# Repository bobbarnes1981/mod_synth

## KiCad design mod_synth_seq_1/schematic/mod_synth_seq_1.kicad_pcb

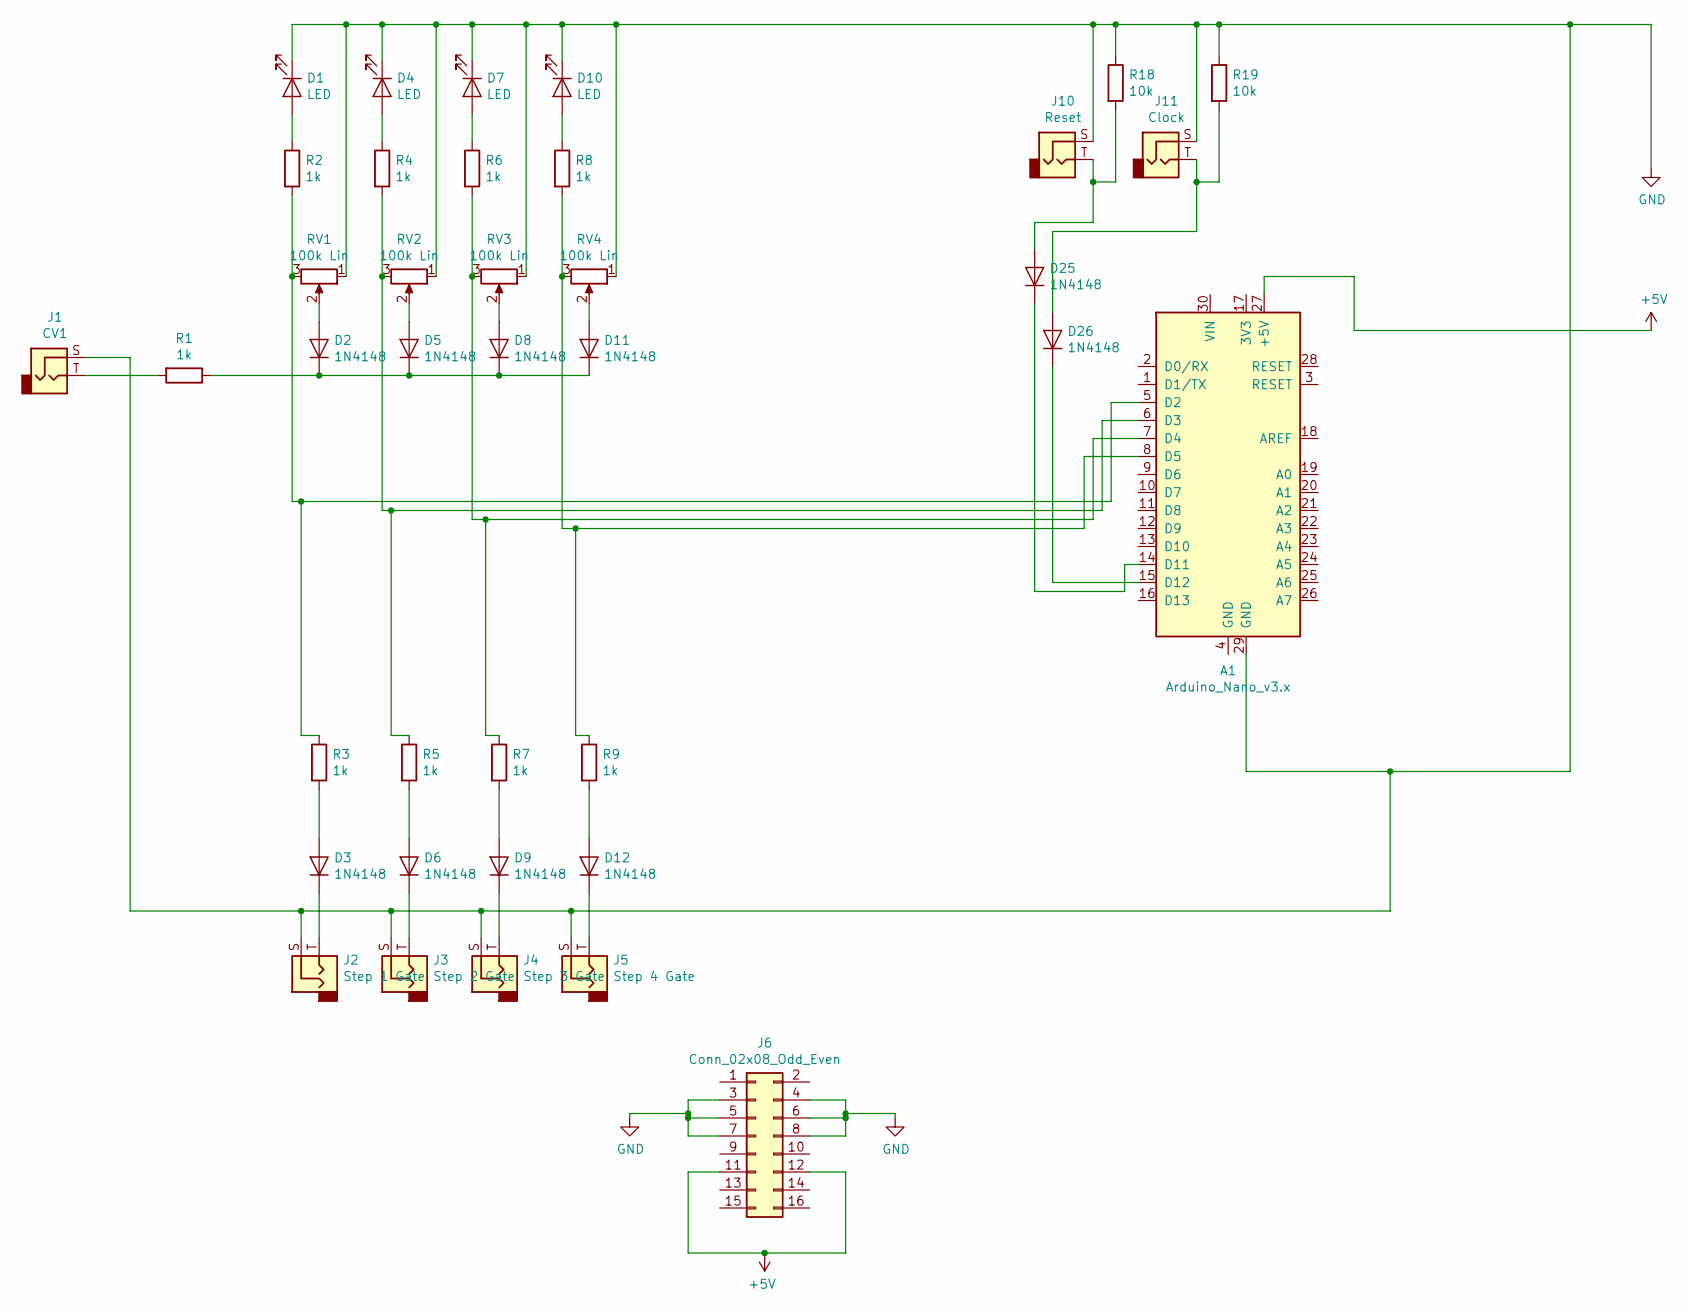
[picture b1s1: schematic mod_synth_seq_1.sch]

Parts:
A1: Arduino_Nano_v3.x; Arduino_Nano
D1, D4, D7, D10: LED; LED_D5.0mm
D2, D3, D5, D6, D8, D9, D11, D12, D25, D26: 1N4148; D_DO-35_SOD27_P7.62mm_Horizontal
J1: CV1; Jack_3.5mm_QingPu_WQP-PJ398SM_Vertical_CircularHoles
J2: Step 1 Gate; Jack_3.5mm_QingPu_WQP-PJ398SM_Vertical_CircularHoles
J3: Step 2 Gate; Jack_3.5mm_QingPu_WQP-PJ398SM_Vertical_CircularHoles
J4: Step 3 Gate; Jack_3.5mm_QingPu_WQP-PJ398SM_Vertical_CircularHoles
J5: Step 4 Gate; Jack_3.5mm_QingPu_WQP-PJ398SM_Vertical_CircularHoles
J6: Conn_02x08_Odd_Even; IDC-Header_2x08_P2.54mm_Vertical
J10: Reset; Jack_3.5mm_QingPu_WQP-PJ398SM_Vertical_CircularHoles
J11: Clock; Jack_3.5mm_QingPu_WQP-PJ398SM_Vertical_CircularHoles
R1, R2, R3, R4, R5, R6, R7, R8, R9: 1k; R_Axial_DIN0207_L6.3mm_D2.5mm_P10.16mm_Horizontal
R18, R19: 10k; R_Axial_DIN0207_L6.3mm_D2.5mm_P10.16mm_Horizontal
RV1, RV2, RV3, RV4: 100k Lin; Potentiometer_Alpha_RD901F-40-00D_Single_Vertical_CircularH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

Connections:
+5V: A1.27 (+5V), J6.11, J6.12
GND: A1.29 (GND), D1.1 (K), D4.1 (K), D7.1 (K), D10.1 (K), J1.S, J2.S, J3.S, J4.S, J5.S, J6.3, J6.4, J6.5, J6.6, J6.7, J6.8, J10.S, J11.S, R18.1, R19.1, RV1.1, RV2.1, RV3.1, RV4.1
unnamed: A1.5 (D2), R2.2, R3.1, RV1.3
unnamed: A1.6 (D3), R4.2, R5.1, RV2.3
unnamed: A1.7 (D4), R6.2, R7.1, RV3.3
unnamed: A1.8 (D5), R8.2, R9.1, RV4.3
unnamed: A1.14 (D11), D25.1 (K)
unnamed: A1.15 (D12), D26.1 (K)
unnamed: D1.2 (A), R2.1
unnamed: D2.2 (A), RV1.2
unnamed: D3.1 (K), J2.T
unnamed: D3.2 (A), R3.2
unnamed: D4.2 (A), R4.1
unnamed: D5.2 (A), RV2.2
unnamed: D6.1 (K), J3.T
unnamed: D6.2 (A), R5.2
unnamed: D7.2 (A), R6.1
unnamed: D8.2 (A), RV3.2
unnamed: D9.1 (K), J4.T
unnamed: D9.2 (A), R7.2
unnamed: D10.2 (A), R8.1
unnamed: D2.1 (K), D5.1 (K), D8.1 (K), D11.1 (K), R1.1
unnamed: D11.2 (A), RV4.2
unnamed: D12.1 (K), J5.T
unnamed: D12.2 (A), R9.2
unnamed: D25.2 (A), J10.T, R18.2
unnamed: D26.2 (A), J11.T, R19.2
unnamed: J1.T, R1.2

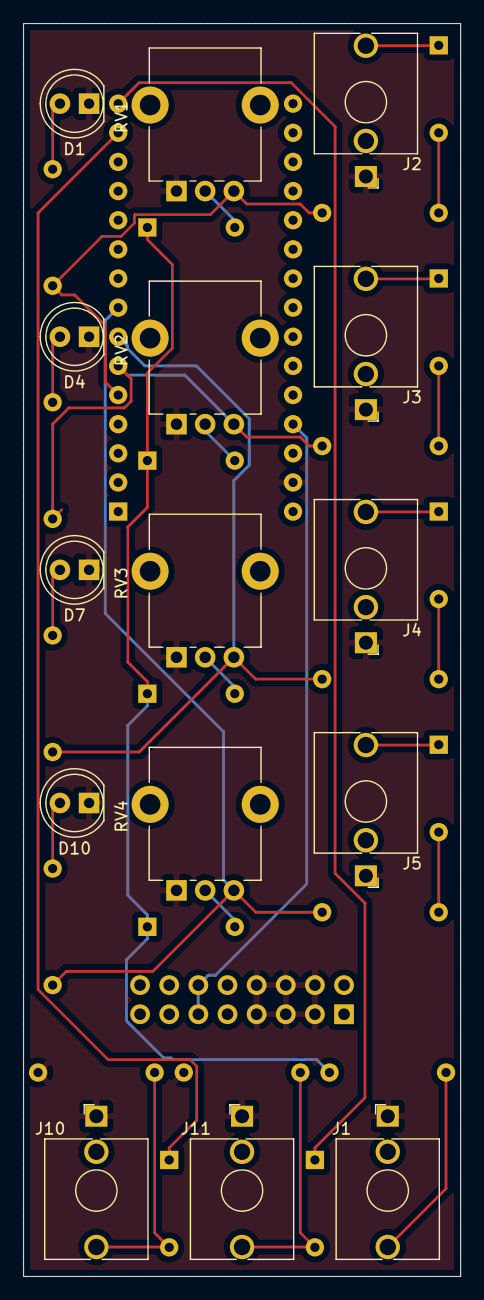
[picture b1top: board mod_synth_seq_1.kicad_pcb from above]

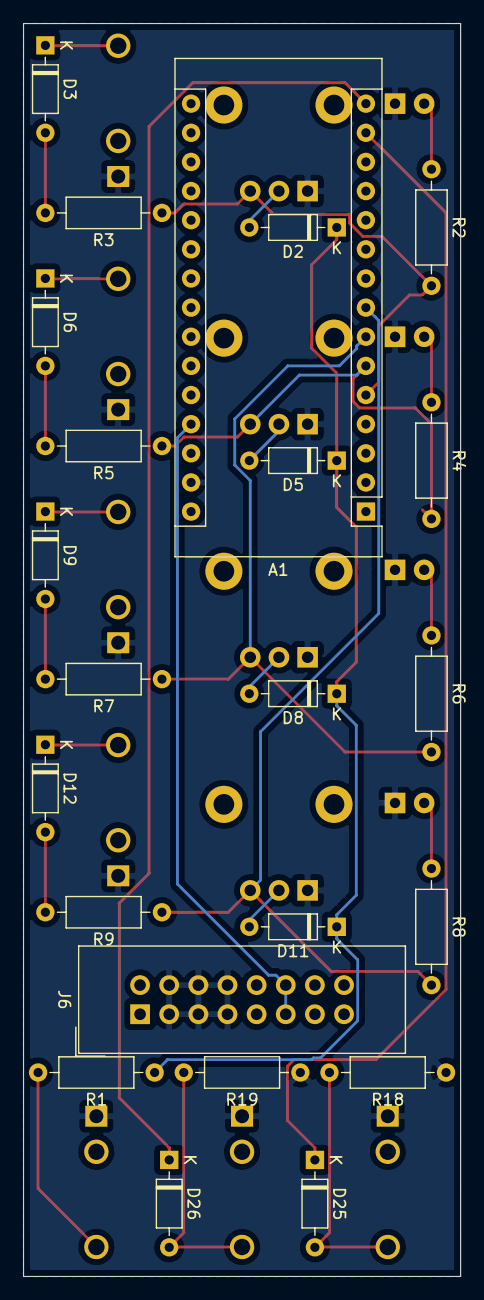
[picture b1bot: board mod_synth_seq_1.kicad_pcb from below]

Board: 2 copper layers, 38.1 x 109.2 mm, 38 parts (23 on the bottom side), 28 nets.

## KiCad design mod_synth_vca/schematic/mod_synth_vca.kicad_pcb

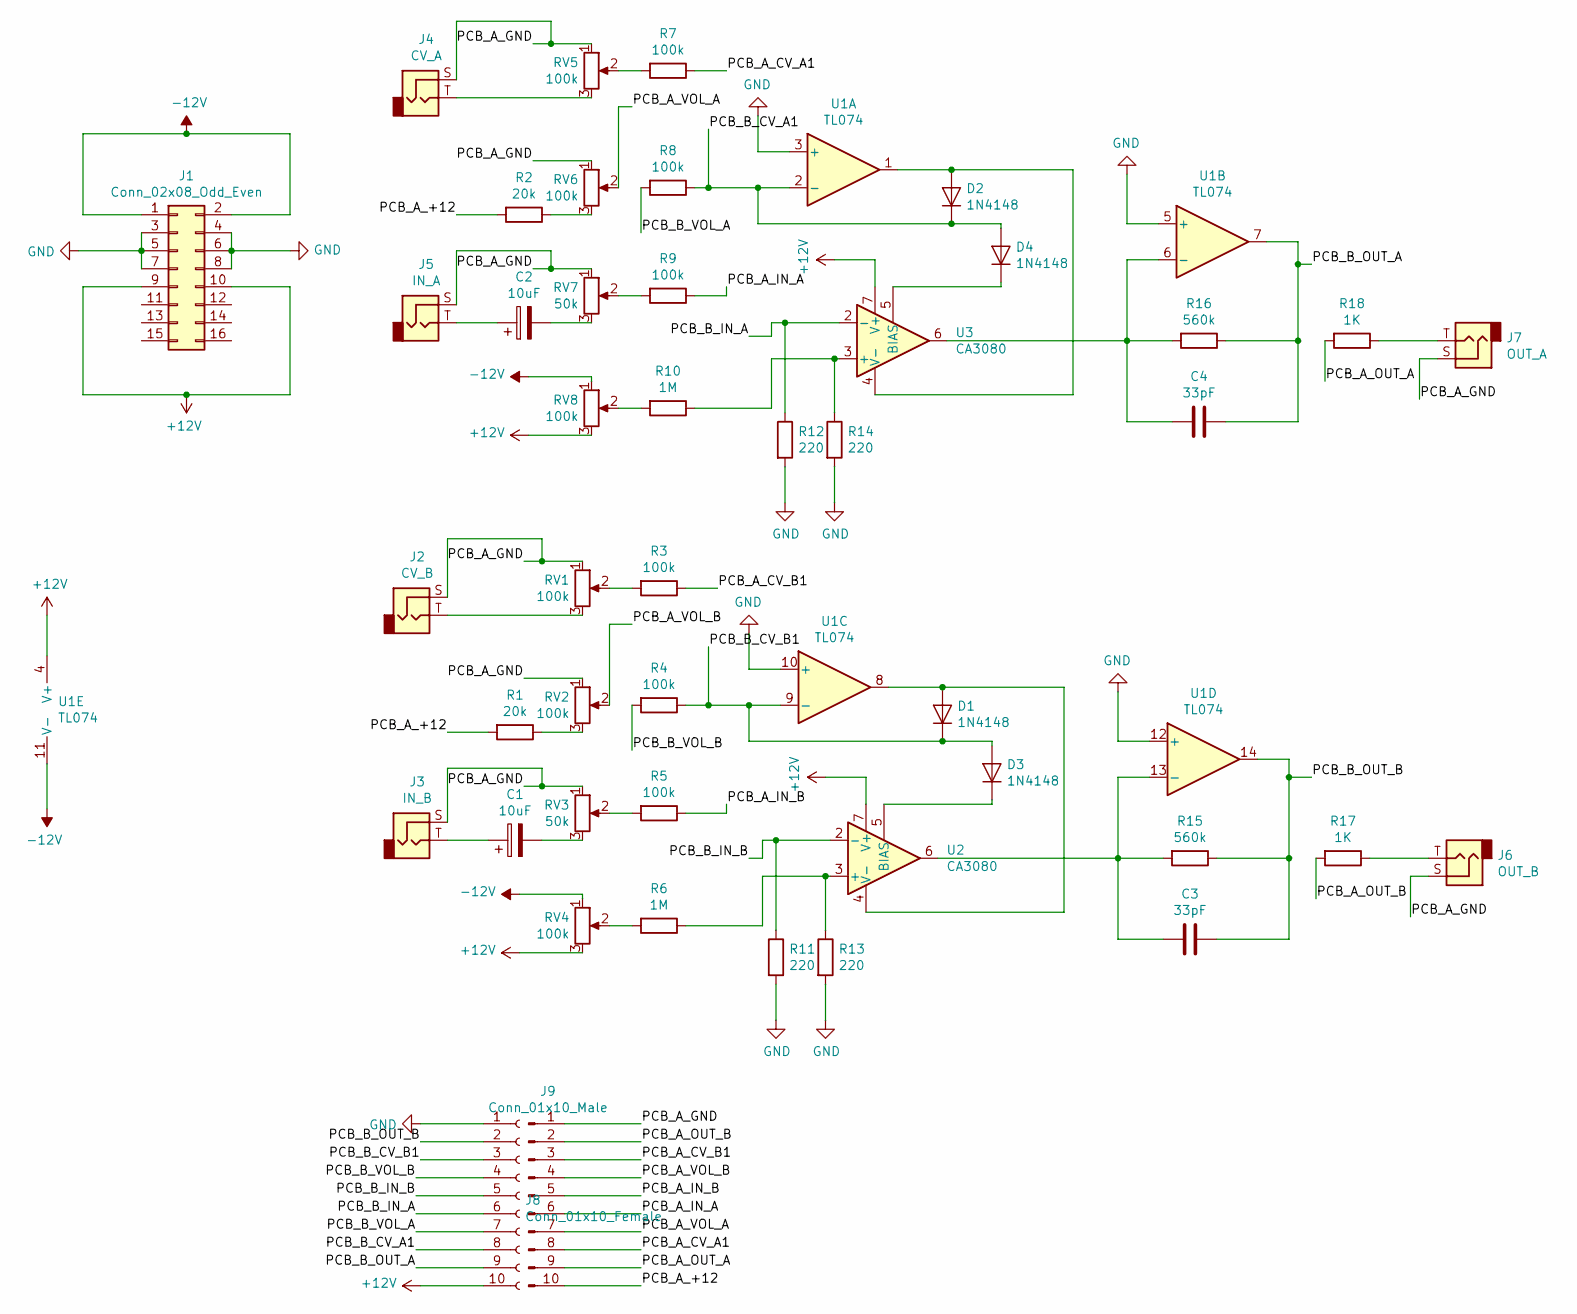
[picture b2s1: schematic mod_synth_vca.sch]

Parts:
C1, C2: 10uF; CP_Radial_D5.0mm_P2.00mm
C3, C4: 33pF; C_Disc_D9.0mm_W2.5mm_P5.00mm
D1, D2, D3, D4: 1N4148; D_DO-35_SOD27_P7.62mm_Horizontal
J1: Conn_02x08_Odd_Even; IDC-Header_2x08_P2.54mm_Vertical
J2: CV_B; Jack_3.5mm_QingPu_WQP-PJ398SM_Vertical_CircularHoles
J3: IN_B; Jack_3.5mm_QingPu_WQP-PJ398SM_Vertical_CircularHoles
J4: CV_A; Jack_3.5mm_QingPu_WQP-PJ398SM_Vertical_CircularHoles
J5: IN_A; Jack_3.5mm_QingPu_WQP-PJ398SM_Vertical_CircularHoles
J6: OUT_B; Jack_3.5mm_QingPu_WQP-PJ398SM_Vertical_CircularHoles
J7: OUT_A; Jack_3.5mm_QingPu_WQP-PJ398SM_Vertical_CircularHoles
J8: Conn_01x10_Female; PinSocket_1x10_P2.54mm_Vertical
J9: Conn_01x10_Male; PinHeader_1x10_P2.54mm_Vertical
R1, R2: 20k; R_Axial_DIN0207_L6.3mm_D2.5mm_P10.16mm_Horizontal
R3, R4, R5, R7, R8, R9: 100k; R_Axial_DIN0207_L6.3mm_D2.5mm_P10.16mm_Horizontal
R6, R10: 1M; R_Axial_DIN0207_L6.3mm_D2.5mm_P10.16mm_Horizontal
R11, R12, R13, R14: 220; R_Axial_DIN0207_L6.3mm_D2.5mm_P10.16mm_Horizontal
R15, R16: 560k; R_Axial_DIN0207_L6.3mm_D2.5mm_P10.16mm_Horizontal
R17, R18: 1K; R_Axial_DIN0207_L6.3mm_D2.5mm_P10.16mm_Horizontal
RV1, RV2, RV5, RV6: 100k; Potentiometer_Alpha_RD901F-40-00D_Single_Vertical_CircularH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
RV3, RV7: 50k; Potentiometer_Alpha_RD901F-40-00D_Single_Vertical_CircularH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
RV4, RV8: 100k; Potentiometer_Runtron_RM-065_Vertical
U1: TL074; DIP-14_W7.62mm_Socket_LongPads
U2, U3: CA3080; DIP-8_W7.62mm_Socket_LongPads

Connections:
+12V: J1.9, J1.10, J8.10, RV4.3, RV8.3, U1.4 (V+), U2.7 (V+), U3.7 (V+)
-12V: J1.1, J1.2, RV4.1, RV8.1, U1.11 (V-)
/PCB_A_+12: J9.10, R1.2, R2.2
/PCB_A_CV_A1: J9.8, R7.1
/PCB_A_CV_B1: J9.3, R3.1
/PCB_A_GND: J2.S, J3.S, J4.S, J5.S, J6.S, J7.S, J9.1, RV1.1, RV2.1, RV3.1, RV5.1, RV6.1, RV7.1
/PCB_A_IN_A: J9.6, R9.1
/PCB_A_IN_B: J9.5, R5.1
/PCB_A_OUT_A: J9.9, R18.2
/PCB_A_OUT_B: J9.2, R17.2
/PCB_A_VOL_A: J9.7, RV6.2
/PCB_A_VOL_B: J9.4, RV2.2
/PCB_B_CV_A1: D2.1 (K), D4.2 (A), J8.8, R8.1, U1.2 (-)
/PCB_B_CV_B1: D1.1 (K), D3.2 (A), J8.3, R4.1, U1.9 (-)
/PCB_B_IN_A: J8.6, R12.1, U3.2 (-)
/PCB_B_IN_B: J8.5, R11.1, U2.2 (-)
/PCB_B_OUT_A: C4.1, J8.9, R16.1, U1.7
/PCB_B_OUT_B: C3.1, J8.2, R15.1, U1.14
/PCB_B_VOL_A: J8.7, R8.2
/PCB_B_VOL_B: J8.4, R4.2
GND: J1.3, J1.4, J1.5, J1.6, J1.7, J1.8, J8.1, R11.2, R12.2, R13.2, R14.2, U1.3 (+), U1.5 (+), U1.10 (+), U1.12 (+)
unnamed: C1.1, J3.T
unnamed: C1.2, RV3.3
unnamed: C2.1, J5.T
unnamed: C2.2, RV7.3
unnamed: C3.2, R15.2, U1.13 (-), U2.6
unnamed: C4.2, R16.2, U1.6 (-), U3.6
unnamed: D1.2 (A), U1.8, U2.4 (V-)
unnamed: D2.2 (A), U1.1, U3.4 (V-)
unnamed: D3.1 (K), U2.5 (BIAS)
unnamed: D4.1 (K), U3.5 (BIAS)
unnamed: J2.T, RV1.3
unnamed: J4.T, RV5.3
unnamed: J6.T, R17.1
unnamed: J7.T, R18.1
unnamed: R1.1, RV2.3
unnamed: R2.1, RV6.3
unnamed: R3.2, RV1.2
unnamed: R5.2, RV3.2
unnamed: R6.2, RV4.2
unnamed: R7.2, RV5.2
unnamed: R9.2, RV7.2
unnamed: R10.1, R14.1, U3.3 (+)
unnamed: R10.2, RV8.2
unnamed: R6.1, R13.1, U2.3 (+)

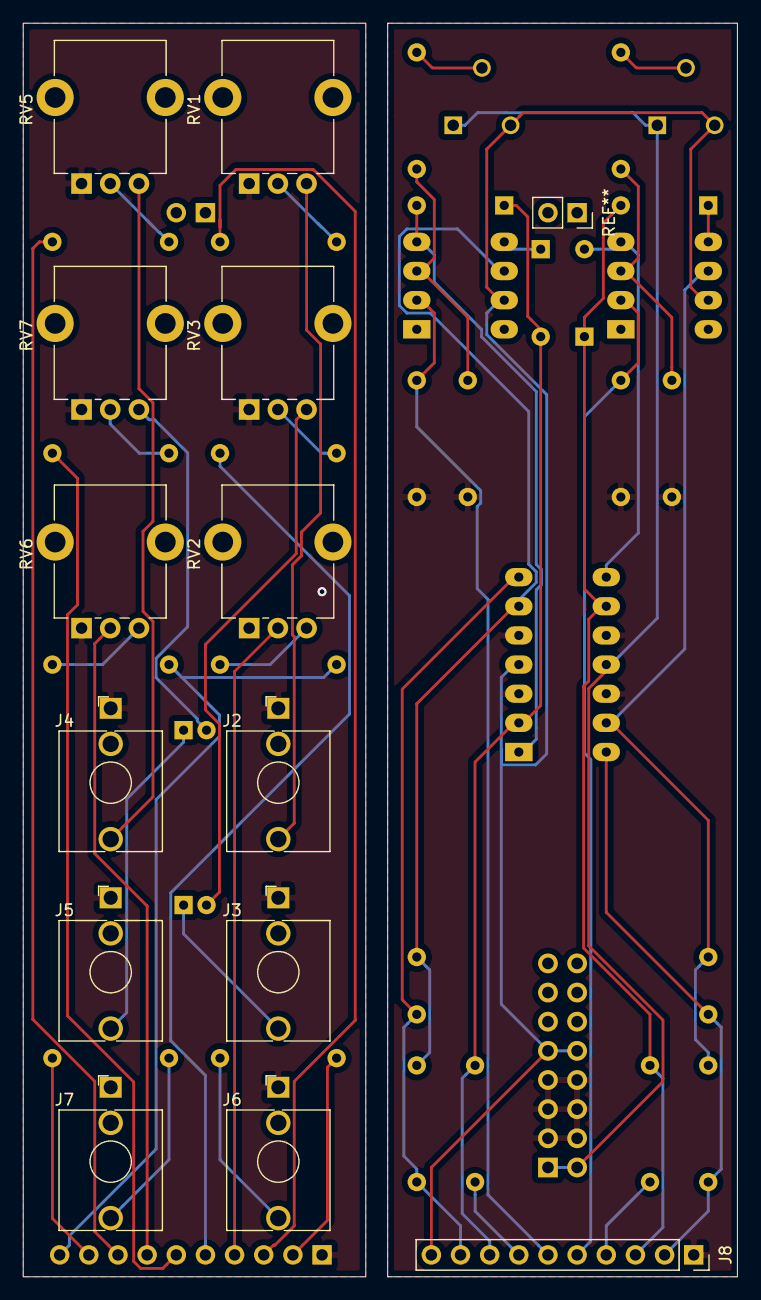
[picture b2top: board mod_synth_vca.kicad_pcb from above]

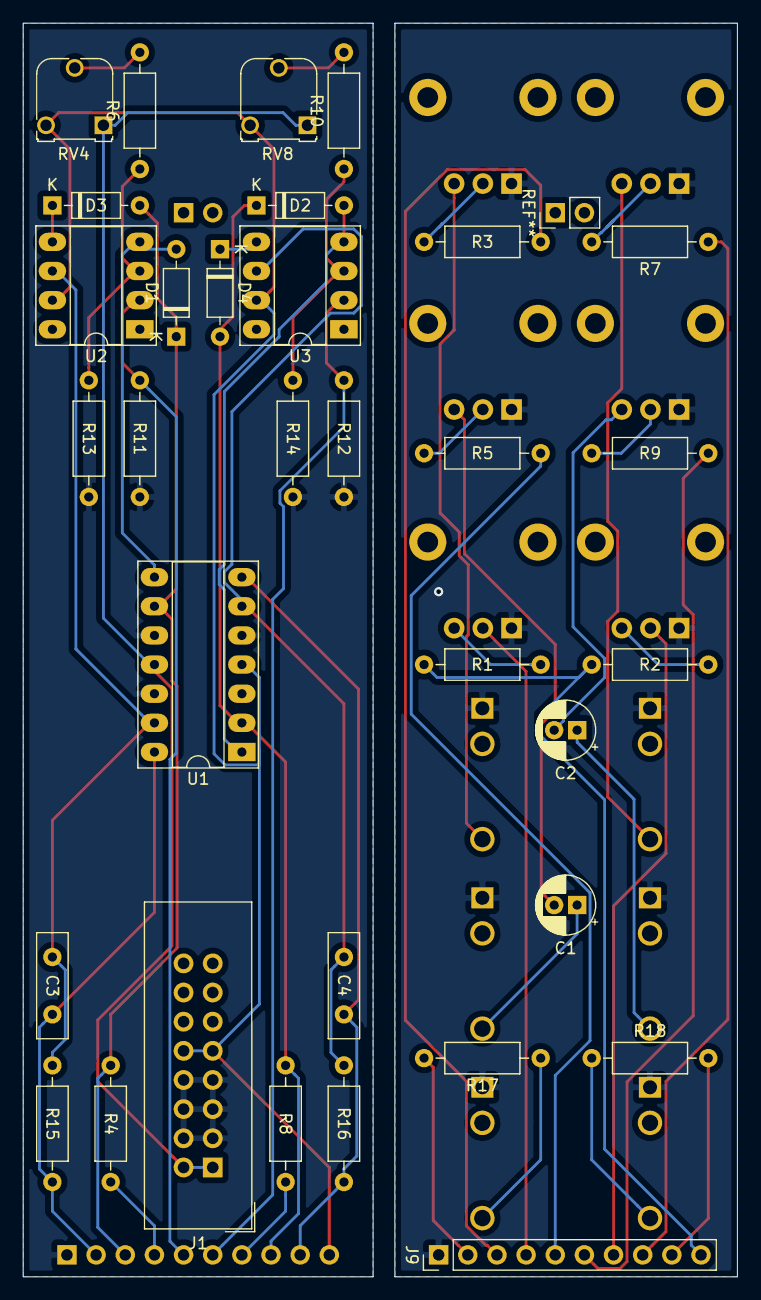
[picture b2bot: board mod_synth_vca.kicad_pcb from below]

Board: 2 copper layers, 62.2 x 109.2 mm, 46 parts (33 on the bottom side), 45 nets.

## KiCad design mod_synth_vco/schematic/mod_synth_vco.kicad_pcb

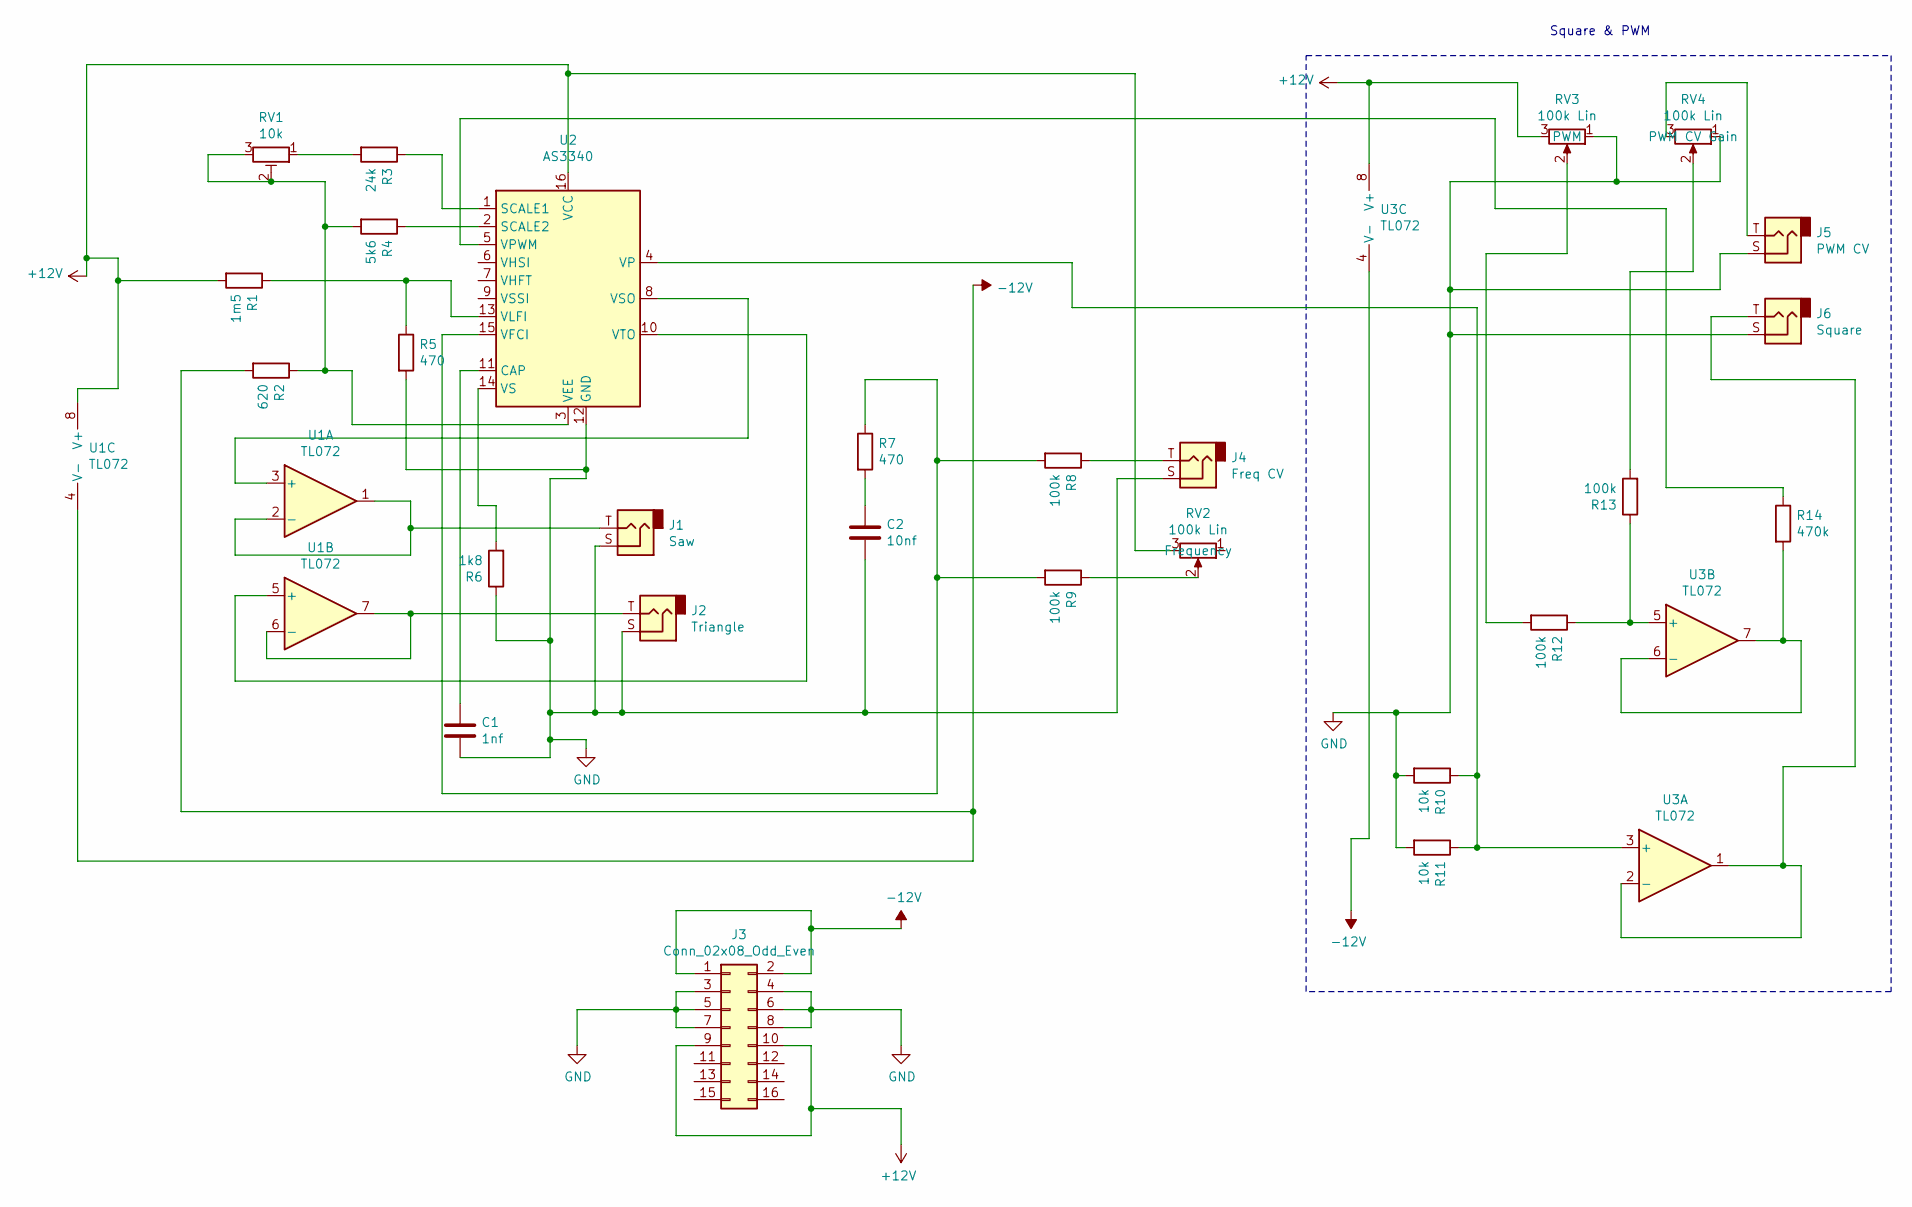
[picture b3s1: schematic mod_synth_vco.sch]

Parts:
C1: 1nf; C_Disc_D9.0mm_W2.5mm_P5.00mm
C2: 10nf; C_Disc_D9.0mm_W2.5mm_P5.00mm
J1: Saw; Jack_3.5mm_QingPu_WQP-PJ398SM_Vertical_CircularHoles
J2: Triangle; Jack_3.5mm_QingPu_WQP-PJ398SM_Vertical_CircularHoles
J3: Conn_02x08_Odd_Even; IDC-Header_2x08_P2.54mm_Vertical
J4: Freq CV; Jack_3.5mm_QingPu_WQP-PJ398SM_Vertical_CircularHoles
J5: PWM CV; Jack_3.5mm_QingPu_WQP-PJ398SM_Vertical_CircularHoles
J6: Square; Jack_3.5mm_QingPu_WQP-PJ398SM_Vertical_CircularHoles
R1: 1m5; R_Axial_DIN0207_L6.3mm_D2.5mm_P10.16mm_Horizontal
R2: 620; R_Axial_DIN0207_L6.3mm_D2.5mm_P10.16mm_Horizontal
R3: 24k; R_Axial_DIN0207_L6.3mm_D2.5mm_P10.16mm_Horizontal
R4: 5k6; R_Axial_DIN0207_L6.3mm_D2.5mm_P10.16mm_Horizontal
R5, R7: 470; R_Axial_DIN0207_L6.3mm_D2.5mm_P10.16mm_Horizontal
R6: 1k8; R_Axial_DIN0207_L6.3mm_D2.5mm_P10.16mm_Horizontal
R8, R9, R12, R13: 100k; R_Axial_DIN0207_L6.3mm_D2.5mm_P10.16mm_Horizontal
R10, R11: 10k; R_Axial_DIN0207_L6.3mm_D2.5mm_P10.16mm_Horizontal
R14: 470k; R_Axial_DIN0207_L6.3mm_D2.5mm_P10.16mm_Horizontal
RV1: 10k; Potentiometer_Runtron_RM-065_Vertical
RV2, RV3, RV4: 100k Lin; Potentiometer_Alpha_RD901F-40-00D_Single_Vertical_CircularH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
U1: TL072; DIP-8_W7.62mm_Socket_LongPads
U2: AS3340; DIP-16_W7.62mm_Socket_LongPads
U3: TL072

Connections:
+12V: J3.9, J3.10, R1.2, RV2.3, RV3.3, U1.8 (V+), U2.16 (VCC), U3.8 (V+)
-12V: J3.1, J3.2, R2.2, U1.4 (V-), U3.4 (V-)
GND: C1.2, C2.2, J1.S, J2.S, J3.3, J3.4, J3.5, J3.6, J3.7, J3.8, J4.S, J5.S, J6.S, R5.2, R6.1, R10.2, R11.2, RV3.1, RV4.1, U2.12 (GND)
unnamed: C1.1, U2.11 (CAP)
unnamed: C2.1, R7.2
unnamed: J1.T, U1.1, U1.2 (-)
unnamed: J2.T, U1.6 (-), U1.7
unnamed: J4.T, R8.1
unnamed: J5.T, RV4.3
unnamed: J6.T, U3.1, U3.2 (-)
unnamed: R1.1, R5.1, U2.13 (VLFI)
unnamed: R2.1, R4.2, RV1.2, RV1.3, U2.3 (VEE)
unnamed: R3.1, U2.1 (SCALE1)
unnamed: R3.2, RV1.1
unnamed: R4.1, U2.2 (SCALE2)
unnamed: R6.2, U2.14 (VS)
unnamed: R7.1, R8.2, R9.2, U2.15 (VFCI)
unnamed: R9.1, RV2.2
unnamed: R10.1, R11.1, U2.4 (VP), U3.3 (+)
unnamed: R12.1, R13.1, U3.5 (+)
unnamed: R12.2, RV3.2
unnamed: R13.2, RV4.2
unnamed: R14.1, U2.5 (VPWM)
unnamed: R14.2, U3.6 (-), U3.7
unnamed: U1.3 (+), U2.8 (VSO)
unnamed: U1.5 (+), U2.10 (VTO)

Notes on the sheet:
Square & PWM

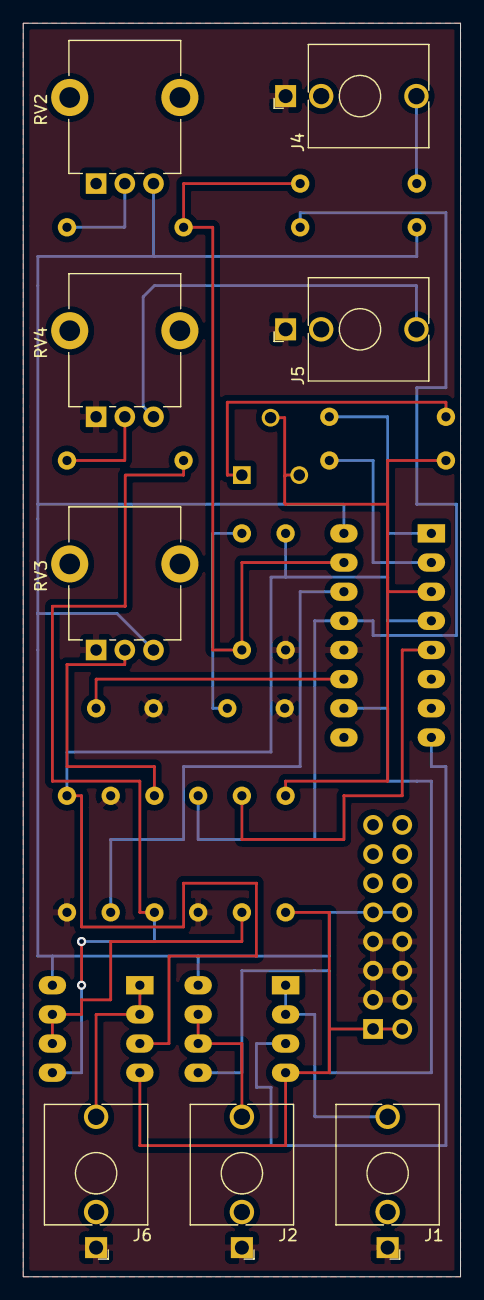
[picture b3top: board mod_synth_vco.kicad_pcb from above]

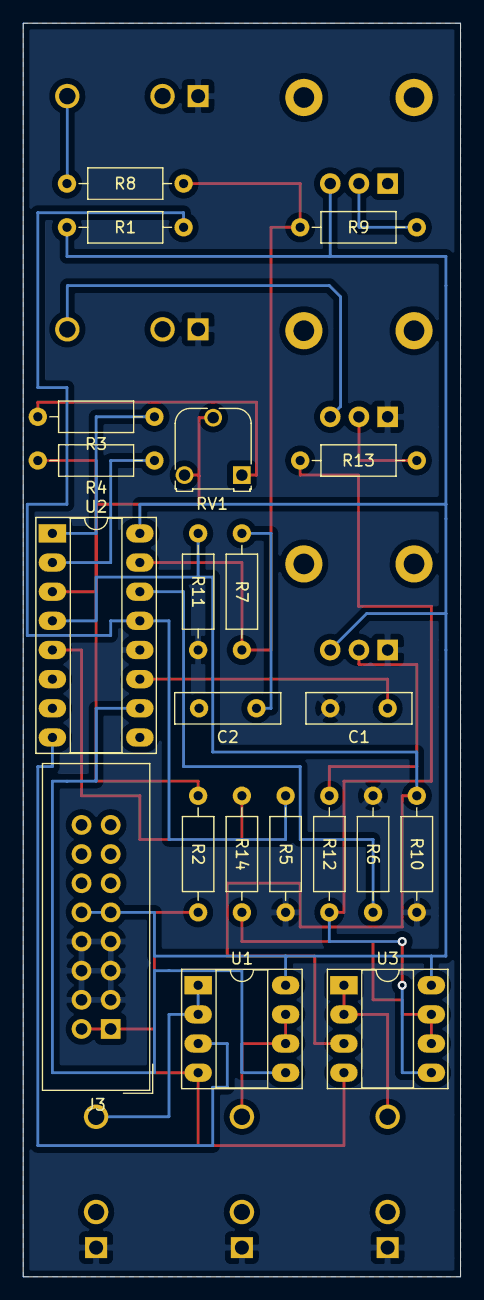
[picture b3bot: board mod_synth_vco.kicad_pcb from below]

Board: 2 copper layers, 38.1 x 109.2 mm, 29 parts (21 on the bottom side), 26 nets.
